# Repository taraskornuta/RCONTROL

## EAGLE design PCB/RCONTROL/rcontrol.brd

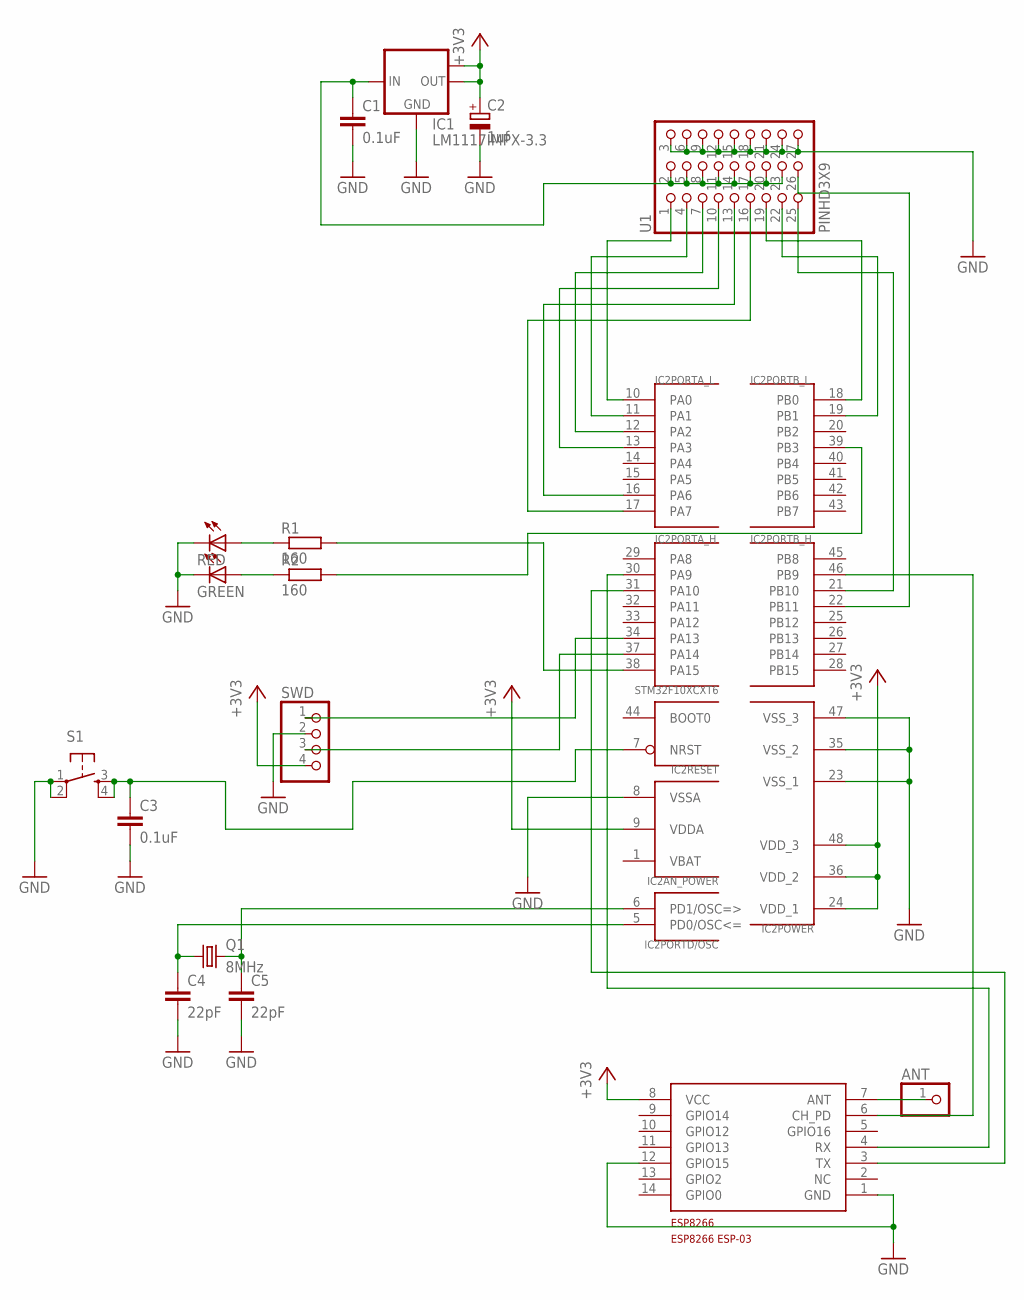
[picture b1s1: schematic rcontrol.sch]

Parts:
ANT: PINHD-1X1; 1X01
C1: 0.1uF; C1206
C2: 1uf; CT3528
C3: 0.1uF; C0805
C4, C5: 22pF; C0805
ESP8266: ESP8266_ESP-03; ESP-03
GREEN: LEDCHIP-LED0805; CHIP-LED0805
IC1: LM1117IMPX-3.3; SOT223
IC2: STM32F10XCXT6; TQFP48
Q1: 8MHz; HC49U-V
R1, R2: 160; R0805
RED: LEDCHIP-LED0805; CHIP-LED0805
S1: TAC_SWITCHSMD; TACTILE_SWITCH_SMD
SWD: PINHD-1X4; 1X04
U1: PINHD3X9; 3X9

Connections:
+3V3: C2.+, ESP8266.8 (VCC), IC1.2 (OUT), IC1.TAB (OUT1), IC2.9 (VDDA), IC2.24 (VDD_1), IC2.36 (VDD_2), IC2.48 (VDD_3), SWD.4
GND: C1.2, C2.-, C3.2, C4.2, C5.2, ESP8266.1 (GND), ESP8266.12 (GPIO15), GREEN.C, IC1.1 (GND), IC2.8 (VSSA), IC2.23 (VSS_1), IC2.35 (VSS_2), IC2.47 (VSS_3), RED.C, S1.1, S1.2, SWD.2, U1.3, U1.6, U1.9, U1.12, U1.15, U1.18, U1.21, U1.24, U1.27
unnamed: IC2.10 (PA0), U1.1
unnamed: IC2.11 (PA1), U1.4
unnamed: IC2.12 (PA2), U1.7
unnamed: IC2.13 (PA3), U1.10
unnamed: IC2.16 (PA6), U1.13
unnamed: C4.1, IC2.5 (PD0/OSC<=), Q1.1
unnamed: IC2.17 (PA7), U1.16
unnamed: IC2.18 (PB0), U1.19
unnamed: ANT.1, ESP8266.7 (ANT)
unnamed: IC2.19 (PB1), U1.22
unnamed: IC2.21 (PB10), U1.25
unnamed: IC2.22 (PB11), U1.26
unnamed: ESP8266.4 (RX), IC2.30 (PA9)
unnamed: ESP8266.3 (TX), IC2.31 (PA10)
unnamed: IC2.34 (PA13), SWD.1
unnamed: IC2.37 (PA14), SWD.3
unnamed: IC2.38 (PA15), R1.2
unnamed: IC2.39 (PB3), R2.2
unnamed: ESP8266.6 (CH_PD), IC2.46 (PB9)
unnamed: R1.1, RED.A
unnamed: GREEN.A, R2.1
unnamed: C1.1, IC1.3 (IN), U1.2, U1.5, U1.8, U1.11, U1.14, U1.17, U1.20, U1.23
unnamed: C3.1, IC2.7 (NRST), S1.3, S1.4
unnamed: C5.1, IC2.6 (PD1/OSC=>), Q1.2
VBAT: IC2.1 (VBAT)

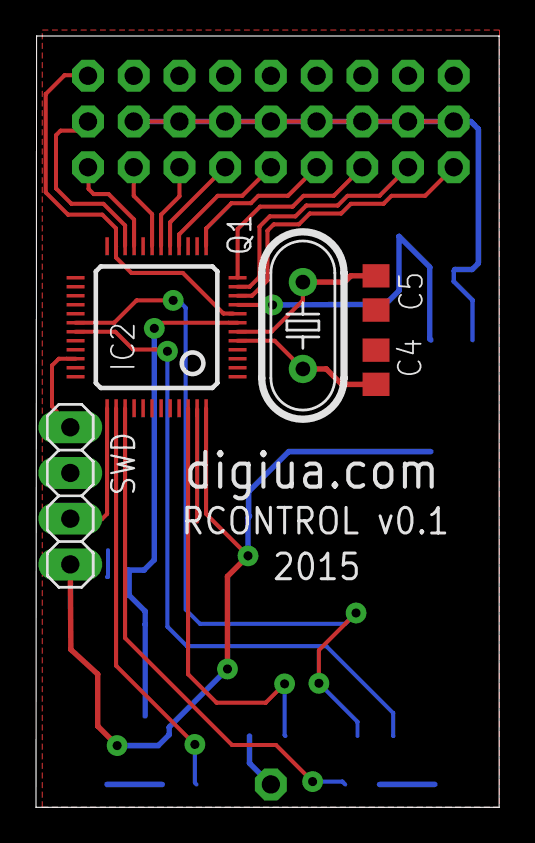
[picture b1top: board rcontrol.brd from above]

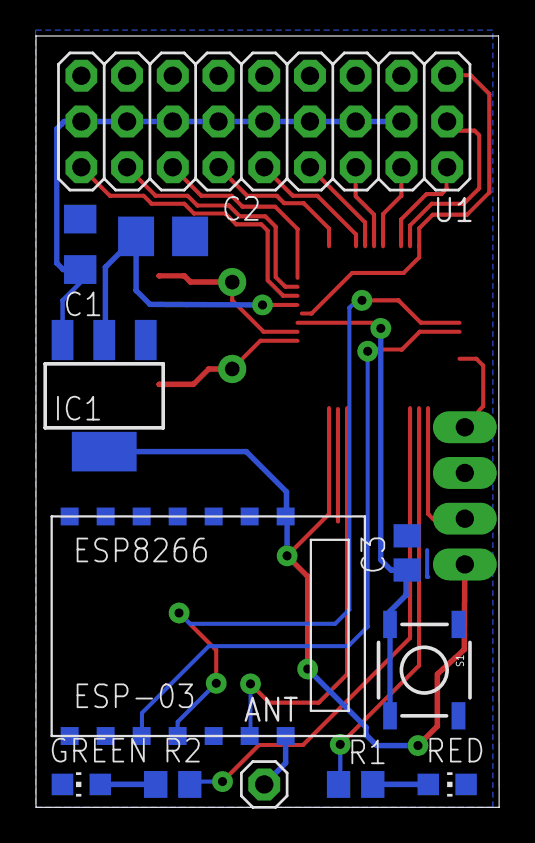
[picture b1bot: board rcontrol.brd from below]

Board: 2 copper layers, 25.7 x 42.9 mm, 17 parts (12 on the bottom side), 26 nets.

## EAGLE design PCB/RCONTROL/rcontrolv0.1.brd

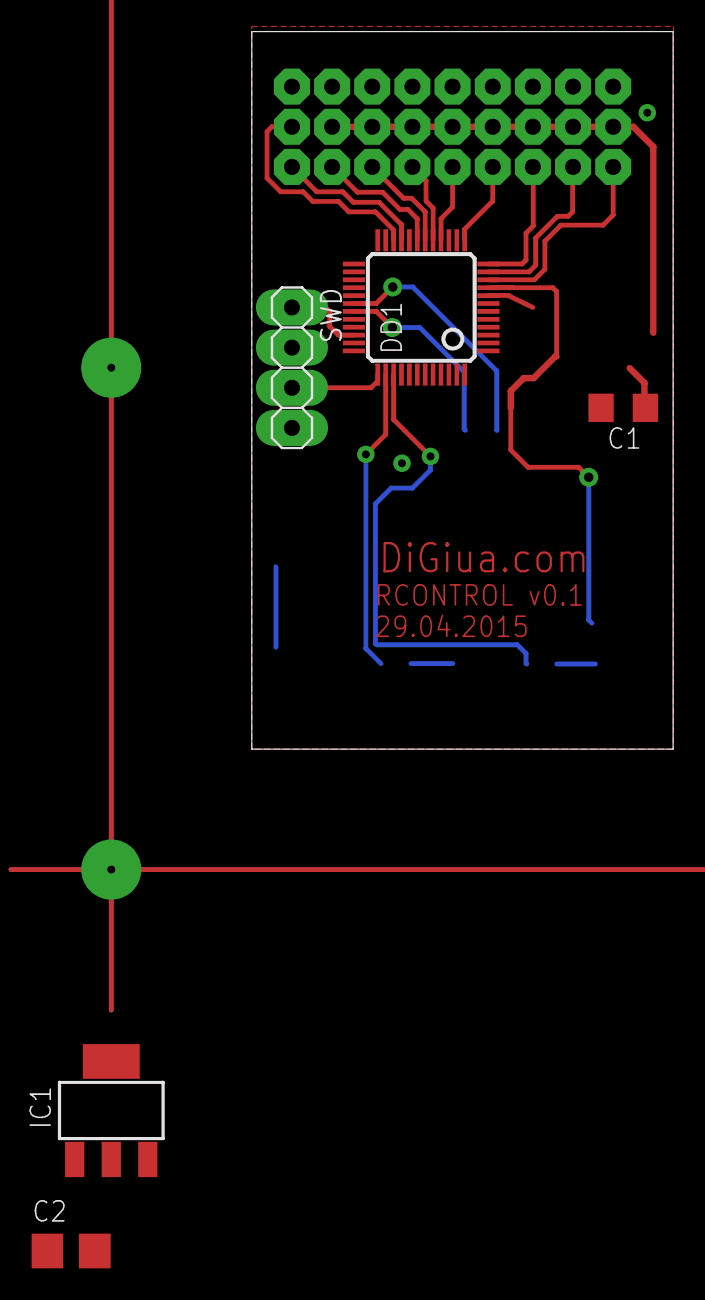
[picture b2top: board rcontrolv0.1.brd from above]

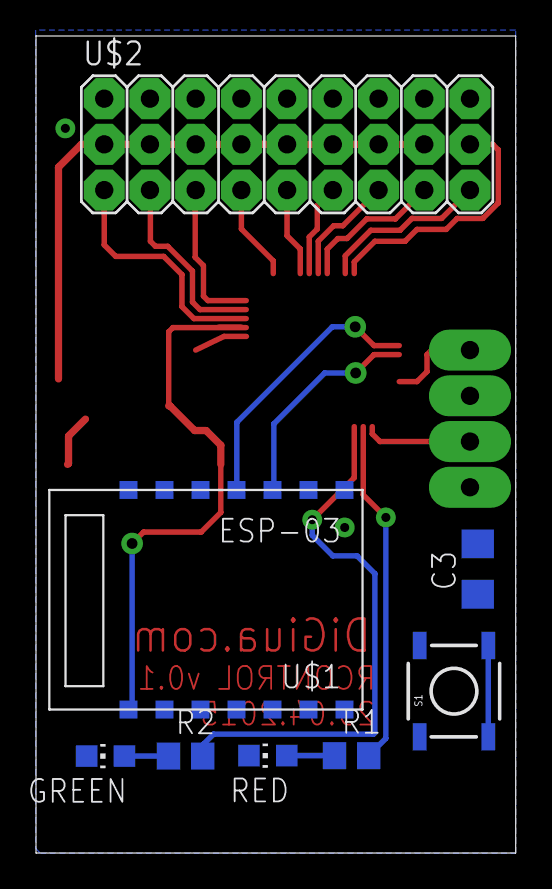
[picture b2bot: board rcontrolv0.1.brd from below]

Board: 2 copper layers, 26.6 x 45.4 mm, 13 parts (8 on the bottom side), 24 nets.

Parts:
C1, C3: 0.1uF; C1206
C2: CT3528
DD1: LQFP48
GREEN: CHIP-LED0805
IC1: LM1117IMPX-3.3; SOT223
R1, R2: 160; R0805
RED: CHIP-LED0805
S1: TACTILE_SWITCH_SMD
SWD: 1X04
U$1: ESP8266_ESP-03; ESP-03
U$2: 3X09

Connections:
+3V3: DD1.9, IC1.TAB, SWD.4, U$1.8
GND: C1.2, C2.-, C3.2, DD1.8, GREEN.C, IC1.1, RED.C, S1.1, S1.2, SWD.2, U$1.1, U$1.12, U$2.3, U$2.6, U$2.9, U$2.12, U$2.15, U$2.18, U$2.021, U$2.24, U$2.27
unnamed: DD1.30, U$1.4
unnamed: DD1.31, U$1.3
unnamed: DD1.37, SWD.3
unnamed: DD1.21, U$2.25
unnamed: DD1.34, SWD.1
unnamed: DD1.38, R1.2
unnamed: DD1.39, R2.2
unnamed: DD1.10, U$2.1
unnamed: DD1.11, U$2.4
unnamed: DD1.12, U$2.7
unnamed: DD1.13, U$2.10
unnamed: DD1.16, U$2.13
unnamed: DD1.17, U$2.16
unnamed: DD1.18, U$2.19
unnamed: DD1.19, U$2.022
unnamed: DD1.22, U$2.26
unnamed: R1.1, RED.A
unnamed: GREEN.A, R2.1
unnamed: C1.1, IC1.3, U$2.2, U$2.5, U$2.8, U$2.11, U$2.14, U$2.17, U$2.020, U$2.023
unnamed: DD1.20, U$1.6
unnamed: C2.+, IC1.2
unnamed: C3.1, DD1.7, S1.3, S1.4

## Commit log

2015-04-29 Create a
2015-04-29 first relise
    first relise
2015-04-29 Revert "Create a"
    This reverts commit effd2470e3c430a3298fd9df2cbeb710e080ad7e.
2015-05-03 New PCB
    New PCB
2015-05-06 UDP Client code update
    Fix several bugs, addet receive udp packets from server
2015-05-12 Porting project to STM32F103C8T6 chip
2015-05-12 Small code format, few files added
2015-06-10 Porting to STM32F103
    LED, esp8266 - now work
2015-06-15 UART1 bug fix
2015-06-15 Small changes in functionaliti
2015-06-15 Revert "UART1 bug fix"
    This reverts commit 92540d2354929773f7d1fb2bdd65a29285816d16.
    Conflicts:
    Firmware/PWM1.cogui
    Firmware/PWM1.comarker
    Firmware/PWM1.coproj
    Firmware/PWM1/Debug/bin/PWM1/Debug/bin/PWM1.bin
2015-06-15 Revert "Revert "UART1 bug fix""
    This reverts commit 387510ae6aeaa5eb32175c1efb420a0d8e3ebfbb.
2015-06-15 Revert "Revert "Revert "UART1 bug fix"""
    This reverts commit f156ce07ae320d8cc7d8c2385d62ef0c2f9d679e.
2015-06-15 nothing new
2015-06-15 not new
2015-06-15 UART2 changet to UART3
2015-06-15 -Wpointer-sign error disabled in compiller
2015-06-15 UART3 bug fix
2015-06-16 small changes
2015-06-17 Axis revers bug fix. Settings form addet
2015-06-18 Addet debug option in Settings form
2015-06-19 Addet custom control, addet limits
2015-06-20 User control bug fix
2015-06-20 Merge remote-tracking branch 'origin/master'
    Conflicts:
    Windows UDP client/esp8266UDP_Client.v11.suo
    Windows UDP client/esp8266UDP_Client/bin/Debug/esp8266UDP_Client.exe
    Windows UDP client/esp8266UDP_Client/bin/Debug/esp8266UDP_Client.pdb
    Windows UDP
    client/esp8266UDP_Client/obj/Debug/esp8266UDP_Client.csproj.GenerateResource.Cache
2015-06-20 Addet controls in Limits panel
2015-06-23 Addet console loging. Addet joystick on/off
2015-06-23 Fixed exception when Debug boxes not filled
2015-06-26 Added icon for program and MainForm
2015-06-29 Merge remote-tracking branch 'origin/master'
    Conflicts:
    Windows UDP client/esp8266UDP_Client.v11.suo
    Windows UDP
    client/esp8266UDP_Client/obj/Release/DesignTimeResolveAssemblyReferences.cache
2015-06-29 Project renamed, custom control have som issues, added for thet new state
2015-06-30 DigitControl (user control) conception changed
    Added timer for auto clicking value, som bug fix
2015-06-30 Added saving the settings in to xml file
2015-07-01 Added class Mixer, for mixing data from joystick, to UDP chanel
2015-07-01 qwww
2015-07-01 qwert
2015-07-12 Added CH_PD - hard reset
2015-07-13 crap
2015-07-13 Changed TIM2 to TIM4, added esp8266 hard reset
2015-07-14 Working on CPPM in CH1
2015-07-15 Warning fix, variable optimization
2015-07-22 Timer fixing timings
2015-07-22 Timer coeffs fix, added test inits
2015-07-27 Little channel structure optimization
2015-07-29 Memory optimization
    Added command --specs=nano.specs to lincer, a lot memory save
2015-07-30 Added som macros for CPPM
2015-07-31 delay_ms - timings fixed
2015-07-31 Added delay_us, cppm - protocol
2015-08-06 CPPM now work
2015-08-07 File structure changed....
    Added CPPM, PWM. c and .h file, for PWM and CPPM protocol. Added
    functions for initialaising PWM or CPPM protokol. WIFI init optimaised.
    Init more cwiclkier
2015-08-07 Fixed bug when MID_Points is newer been in center 1500
2015-08-23 Changed joystick driver to DirectX.Direct Input, code cleanup
2015-08-25 Added jumper state to chose PWM or CPPM protocols, code optimization
    Added jumper to GPIOA Pin1. Both protocol now work. In jumper connect to
    GPIOA Pin1 and GPIOA Pin2, CPPM - is work. If jumper disconnected 8
    analog pwm servo channels is on
2015-08-25 UI changed, icons changed
2015-08-31 Jumper_state bug-fix

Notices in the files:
parts and their libraries:
SparkFun-Electromechanical: Licensing: Creative Commons ShareAlike 4.0 International - https://creativecommons.org/licenses/by-sa/4.0
